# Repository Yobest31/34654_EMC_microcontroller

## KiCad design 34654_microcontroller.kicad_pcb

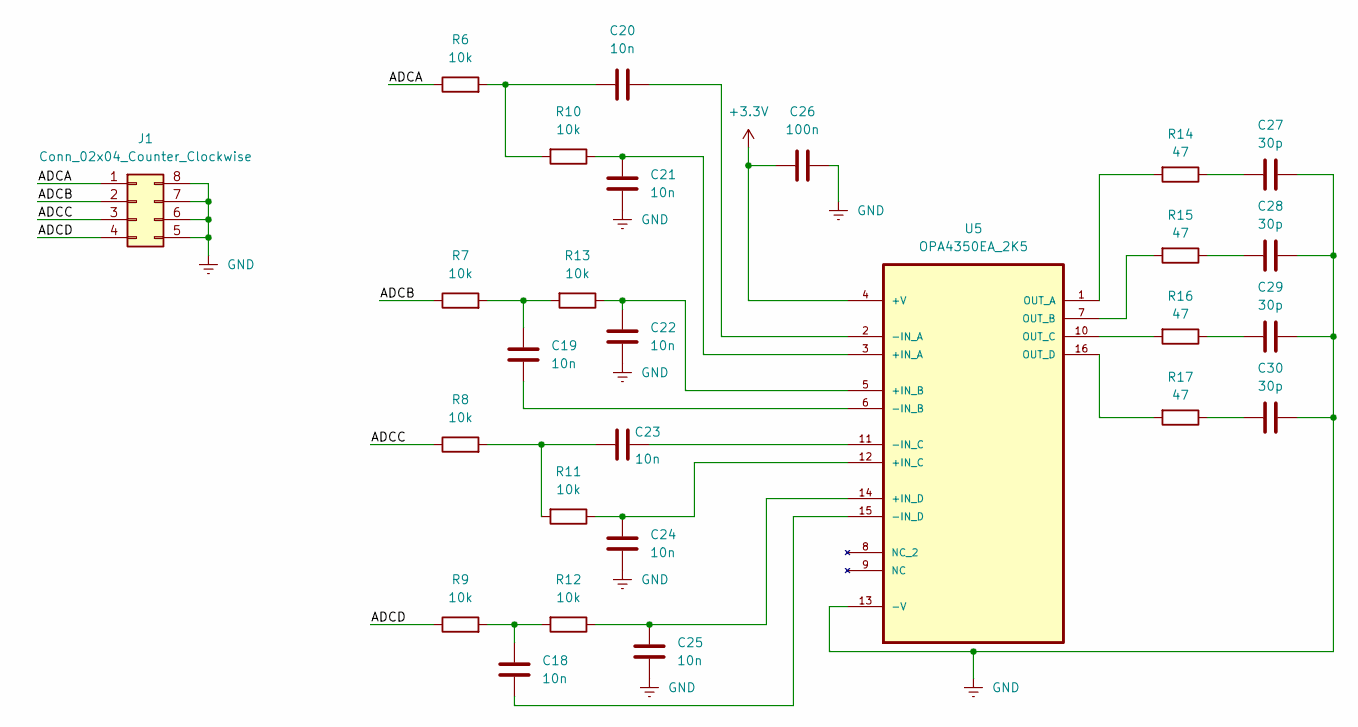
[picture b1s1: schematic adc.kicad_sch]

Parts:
C18, C19, C20, C21, C22, C23, C24, C25: 10n; C_0805_2012Metric
C26: 100n; C_0805_2012Metric
C27, C28, C29, C30: 30p; C_0805_2012Metric
J1: Conn_02x04_Counter_Clockwise; IDC-Header_2x04_P2.54mm_Vertical
R6, R7, R8, R9, R10, R11, R12, R13: 10k; R_0805_2012Metric
R14, R15, R16, R17: 47; R_0805_2012Metric
U5: OPA4350EA_2K5; SOP63P600X175-16N; MPN OPA4350EA/2K5

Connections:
+3.3V: C26.2, U5.4 (+V); also elsewhere on the board
/ADC/ADCA: J1.1, R6.1
/ADC/ADCB: J1.2, R7.1
/ADC/ADCC: J1.3, R8.1
/ADC/ADCD: J1.4, R9.1
GND: C21.2, C22.2, C24.2, C25.2, C26.1, C27.1, C28.1, C29.1, C30.1, J1.5, J1.6, J1.7, J1.8, U5.13 (-V); also elsewhere on the board
unnamed: C18.2, R9.2, R12.2
unnamed: C19.2, R7.2, R13.2
unnamed: C20.2, R6.2, R10.2
unnamed: C23.2, R8.2, R11.2
unnamed: C27.2, R14.1
unnamed: C28.2, R15.1
unnamed: C29.2, R16.1
unnamed: C30.2, R17.1
unnamed: C21.1, R10.1, U5.3 (+IN_A)
unnamed: C22.1, R13.1, U5.5 (+IN_B)
unnamed: C24.1, R11.1, U5.12 (+IN_C)
unnamed: C25.1, R12.1, U5.14 (+IN_D)
unnamed: C20.1, U5.2 (-IN_A)
unnamed: C19.1, U5.6 (-IN_B)
unnamed: C23.1, U5.11 (-IN_C)
unnamed: C18.1, U5.15 (-IN_D)
unnamed: R14.2, U5.1 (OUT_A)
unnamed: R15.2, U5.7 (OUT_B)
unnamed: R16.2, U5.10 (OUT_C)
unnamed: R17.2, U5.16 (OUT_D)

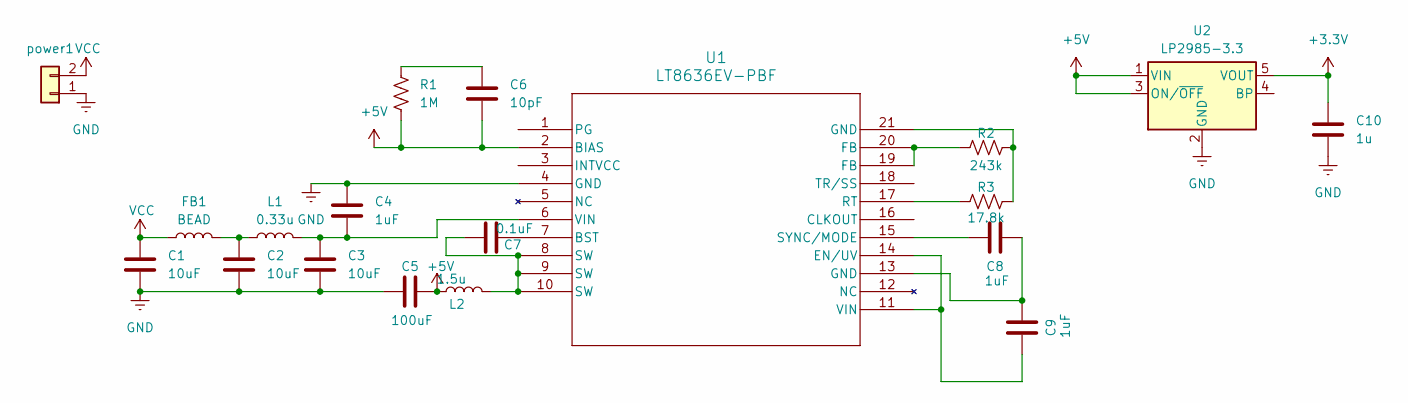
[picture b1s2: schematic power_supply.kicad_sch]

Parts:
C1, C2, C3: 10uF; C_0805_2012Metric
C4, C8, C9: 1uF; C_0805_2012Metric
C5: 100uF; C_1206_3216Metric
C6: 10pF; C_0805_2012Metric
C7: 0.1uF; C_0805_2012Metric
C10: 1u; C_0805_2012Metric
FB1: BEAD; BEADC2012X105N
L1: 0.33u; C_0805_2012Metric
L2: 1.5u; L_0805_2012Metric
R1: 1M; R_0805_2012Metric
R2: 243k; R_0805_2012Metric
R3: 17.8k; R_0805_2012Metric
U1: LT8636EV-PBF; QFN50P400X300X94-25N
U2: LP2985-3.3; SOT-23-5
power1: Conn_01x02; AMASS_XT60-M_1x02_P7.20mm_Vertical

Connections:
+3.3V: C10.1, U2.5 (VOUT); also elsewhere on the board
+5V: C5.2, C6.2, L2.1, R1.2, U1.2 (BIAS), U2.1 (VIN), U2.3 (ON/~OFF); also elsewhere on the board
GND: C1.2, C2.2, C3.2, C4.1, C5.1, C10.2, U1.4 (GND), U2.2 (GND), power1.1; also elsewhere on the board
unnamed: C2.1, FB1.2, L1.1
unnamed: C3.1, C4.2, L1.2, U1.6 (VIN)
unnamed: C6.1, R1.1
unnamed: C7.1, L2.2, U1.8 (SW), U1.9 (SW), U1.10 (SW)
unnamed: C8.2, C9.2, U1.13 (GND)
unnamed: R2.1, U1.19 (FB), U1.20 (FB)
unnamed: R2.2, R3.2, U1.21 (GND)
unnamed: C7.2, U1.7 (BST)
unnamed: C9.1, U1.11 (VIN), U1.14 (EN/UV)
unnamed: R3.1, U1.17 (RT)
unnamed: C8.1, U1.15 (SYNC/MODE)
VCC: C1.1, FB1.1, power1.2

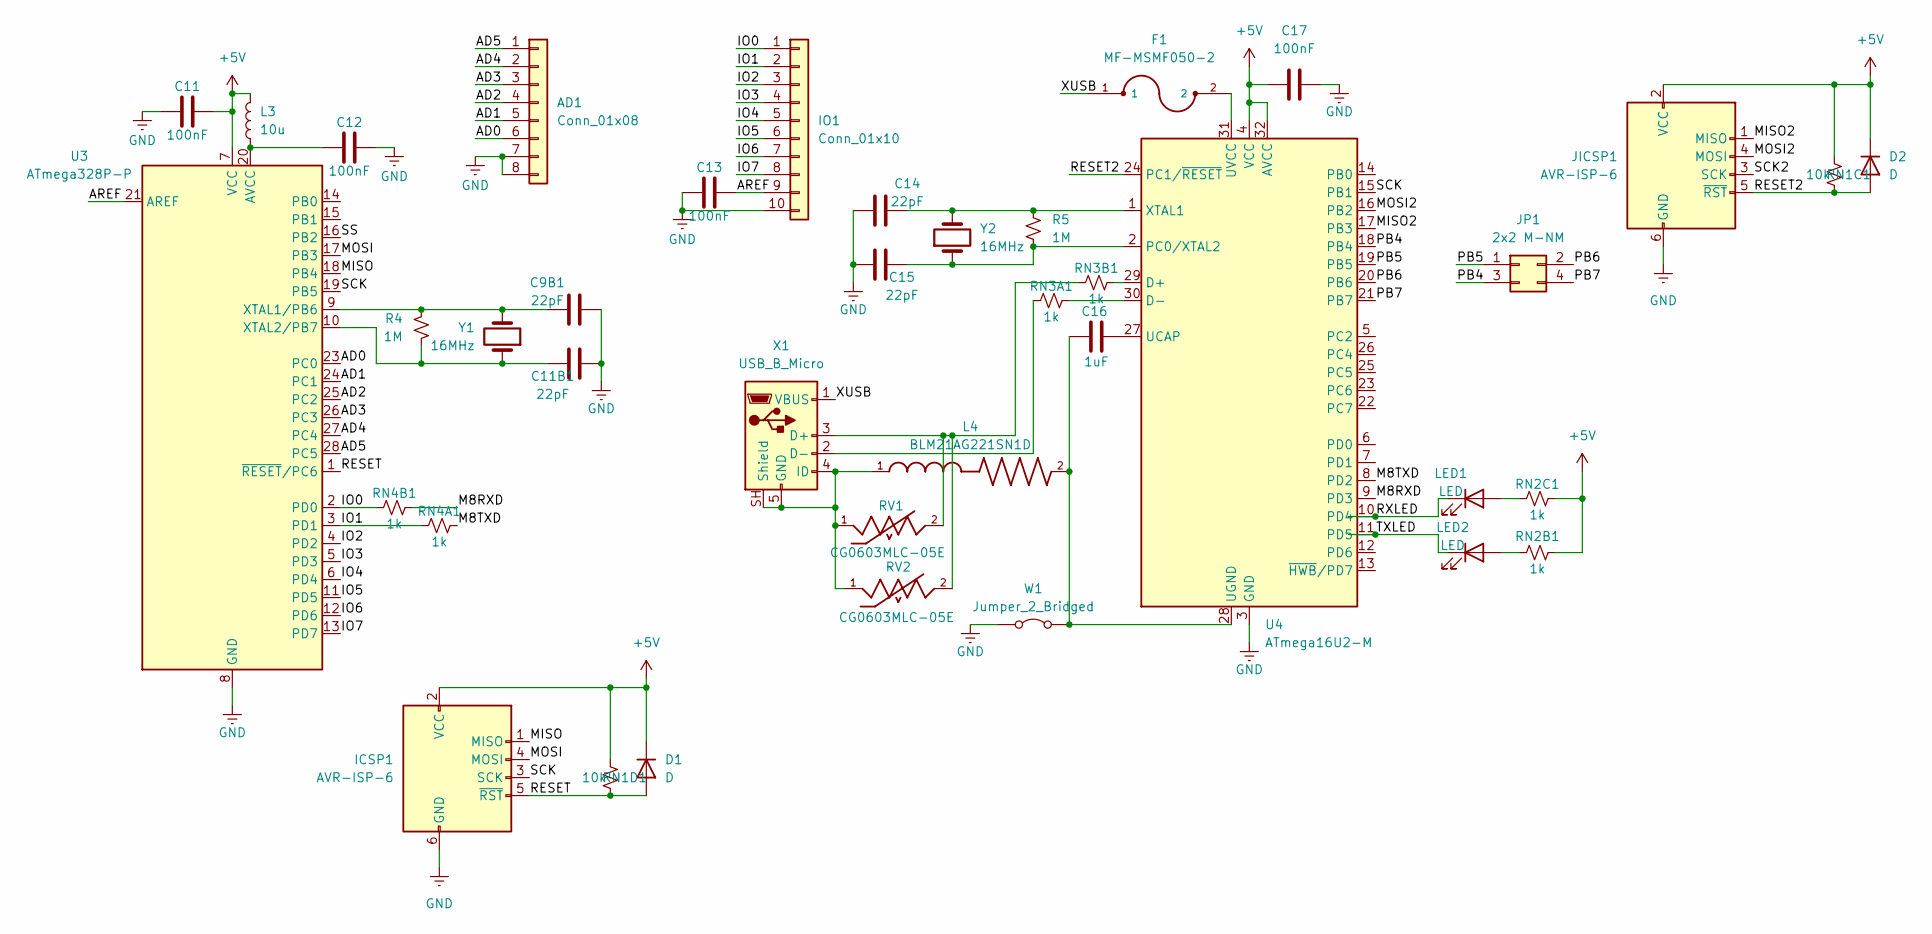
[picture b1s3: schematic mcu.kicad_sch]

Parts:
AD1: Conn_01x08; PinSocket_1x08_P2.54mm_Vertical
C9B1, C11B1, C14, C15: 22pF; C_0805_2012Metric
C11, C12, C13, C17: 100nF; C_1206_3216Metric
C16: 1uF; C_1206_3216Metric
D1, D2: D; D_0805_2012Metric
F1: MF-MSMF050-2; FUSM4632X85
ICSP1: AVR-ISP-6; PinHeader_2x03_P2.54mm_Vertical
IO1: Conn_01x10; PinSocket_1x10_P2.54mm_Vertical
JICSP1: AVR-ISP-6; PinHeader_2x03_P2.54mm_Vertical
JP1: 2x2 M-NM; PinHeader_2x02_P2.54mm_Vertical
L3: 10u; L_0805_2012Metric
L4: BLM21AG221SN1D; BEADC2012X105N
LED1, LED2: LED; LED_0805_2012Metric
R4, R5: 1M; R_0805_2012Metric
RN1C1, RN1D1: 10k; R_0805_2012Metric
RN2B1, RN2C1, RN3A1, RN3B1, RN4A1, RN4B1: 1k; R_0805_2012Metric
RV1, RV2: CG0603MLC-05E; VARC1608X56N; PARTREV E
U3: ATmega328P-P; DIP-28_W7.62mm
U4: ATmega16U2-M; QFN-32-1EP_5x5mm_P0.5mm_EP3.1x3.1mm
W1: Jumper_2_Bridged; PinHeader_1x02_P2.54mm_Vertical
X1: USB_B_Micro; USB_Micro-B_Wuerth_629105150521
Y1, Y2: 16MHz; Crystal_SMD_MicroCrystal_CC8V-T1A-2Pin_2.0x1.2mm

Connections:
+5V: C11.2, C17.1, D1.1 (K), D2.1 (K), ICSP1.2 (VCC), JICSP1.2 (VCC), L3.2, RN1C1.1, RN1D1.1, RN2B1.2, RN2C1.2, U3.7 (VCC), U4.4 (VCC), U4.32 (AVCC); also elsewhere on the board
/MCU/AD0: AD1.6, U3.23 (PC0)
/MCU/AD1: AD1.5, U3.24 (PC1)
/MCU/AD2: AD1.4, U3.25 (PC2)
/MCU/AD3: AD1.3, U3.26 (PC3)
/MCU/AD4: AD1.2, U3.27 (PC4)
/MCU/AD5: AD1.1, U3.28 (PC5)
/MCU/AREF: C13.2, IO1.9, U3.21 (AREF)
/MCU/IO0: IO1.1, RN4B1.1, U3.2 (PD0)
/MCU/IO1: IO1.2, RN4A1.1, U3.3 (PD1)
/MCU/IO2: IO1.3, U3.4 (PD2)
/MCU/IO3: IO1.4, U3.5 (PD3)
/MCU/IO4: IO1.5, U3.6 (PD4)
/MCU/IO5: IO1.6, U3.11 (PD5)
/MCU/IO6: IO1.7, U3.12 (PD6)
/MCU/IO7: IO1.8, U3.13 (PD7)
/MCU/M8RXD: RN4B1.2, U4.9 (PD3)
/MCU/M8TXD: RN4A1.2, U4.8 (PD2)
/MCU/MISO: ICSP1.1 (MISO), U3.18 (PB4)
/MCU/MISO2: JICSP1.1 (MISO), U4.17 (PB3); also elsewhere on the board
/MCU/MOSI: ICSP1.4 (MOSI), U3.17 (PB3)
/MCU/MOSI2: JICSP1.4 (MOSI), U4.16 (PB2); also elsewhere on the board
/MCU/PB4: JP1.3, U4.18 (PB4)
/MCU/PB5: JP1.1, U4.19 (PB5)
/MCU/PB6: JP1.2, U4.20 (PB6)
/MCU/PB7: JP1.4, U4.21 (PB7)
/MCU/RESET: D1.2 (A), ICSP1.5 (~RST), RN1D1.2, U3.1 (~RESET/PC6)
/MCU/RESET2: D2.2 (A), JICSP1.5 (~RST), RN1C1.2, U4.24 (PC1/~RESET); also elsewhere on the board
/MCU/RXLED: LED1.1 (K), U4.10 (PD4)
/MCU/SCK: ICSP1.3 (SCK), U3.19 (PB5), U4.15 (PB1)
/MCU/SS: U3.16 (PB2)
/MCU/TXLED: LED2.1 (K), U4.11 (PD5)
/MCU/XUSB: F1.1, X1.1 (VBUS)
GND: AD1.7, AD1.8, C9B1.1, C11.1, C11B1.1, C12.2, C13.1, C14.1, C15.1, C17.2, ICSP1.6 (GND), IO1.10, JICSP1.6 (GND), U3.8 (GND), U3.22 (GND), U4.3 (GND), U4.33 (GND), W1.1 (A); also elsewhere on the board
unnamed: LED1.2 (A), RN2C1.1
unnamed: LED2.2 (A), RN2B1.1
unnamed: C12.1, L3.1, U3.20 (AVCC)
unnamed: C9B1.2, R4.1, U3.9 (XTAL1/PB6), Y1.2
unnamed: C11B1.2, R4.2, U3.10 (XTAL2/PB7), Y1.1
unnamed: RN3B1.2, U4.29 (D+)
unnamed: RN3A1.2, U4.30 (D-)
unnamed: C15.2, R5.2, U4.2 (PC0/XTAL2), Y2.1
unnamed: C16.2, U4.27 (UCAP)
unnamed: C16.1, L4.2, U4.28 (UGND), W1.2 (B)
unnamed: F1.2, U4.31 (UVCC)
unnamed: C14.2, R5.1, U4.1 (XTAL1), Y2.2
unnamed: RN3B1.1, RV1.2, RV2.2, X1.3 (D+)
unnamed: RN3A1.1, X1.2 (D-)
unnamed: L4.1, RV1.1, RV2.1, X1.4 (ID), X1.5 (GND), X1.SH (Shield)

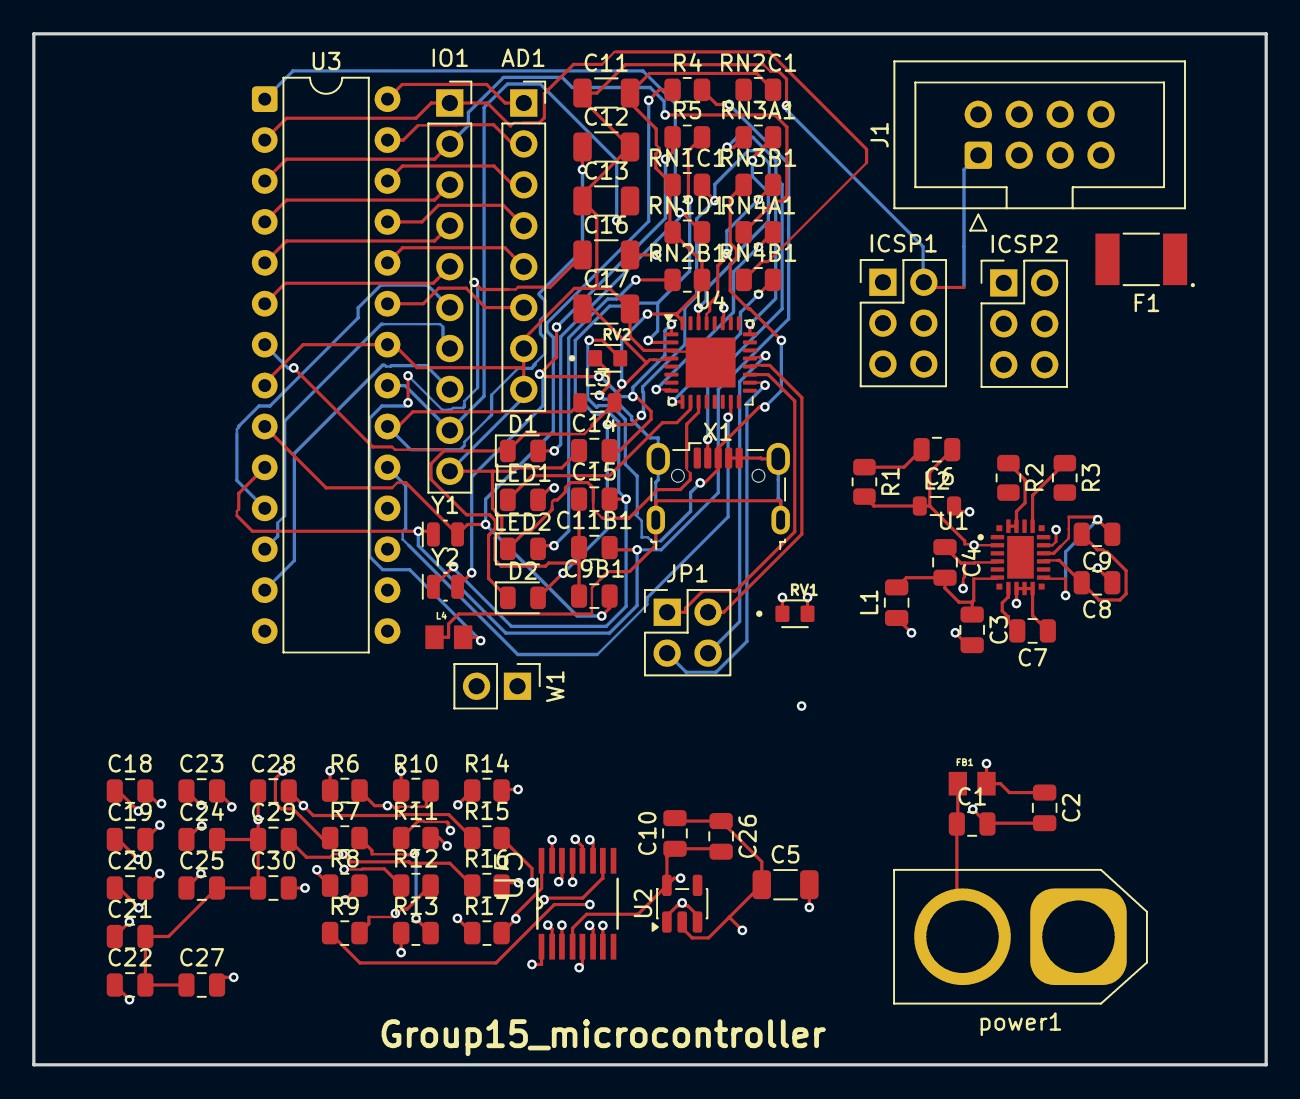
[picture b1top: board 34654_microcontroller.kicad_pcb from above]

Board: 4 copper layers, 76.5 x 64.0 mm, 85 parts (0 on the bottom side), 85 nets.

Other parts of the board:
ICSP2: AVR-ISP-6; PinHeader_2x03_P2.54mm_Vertical

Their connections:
+5V: ICSP2.2 (VCC); also elsewhere on the board
/MCU/MISO2: ICSP2.1 (MISO); also elsewhere on the board
/MCU/MOSI2: ICSP2.4 (MOSI); also elsewhere on the board
/MCU/RESET2: ICSP2.5 (~RST); also elsewhere on the board
GND: ICSP2.6 (GND); also elsewhere on the board
